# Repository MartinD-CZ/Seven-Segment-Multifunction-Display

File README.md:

# Seven Segment Multifunction Display
*see the article [here](http://embedblog.eu/?p=282)*

## Description
A simple project, based on the ATmega88. Can show analog voltage in two ranges (0 - 6 V or 0 - 30 V) with < 1 % accuracy or can display characters sent to it via UART/I2C.

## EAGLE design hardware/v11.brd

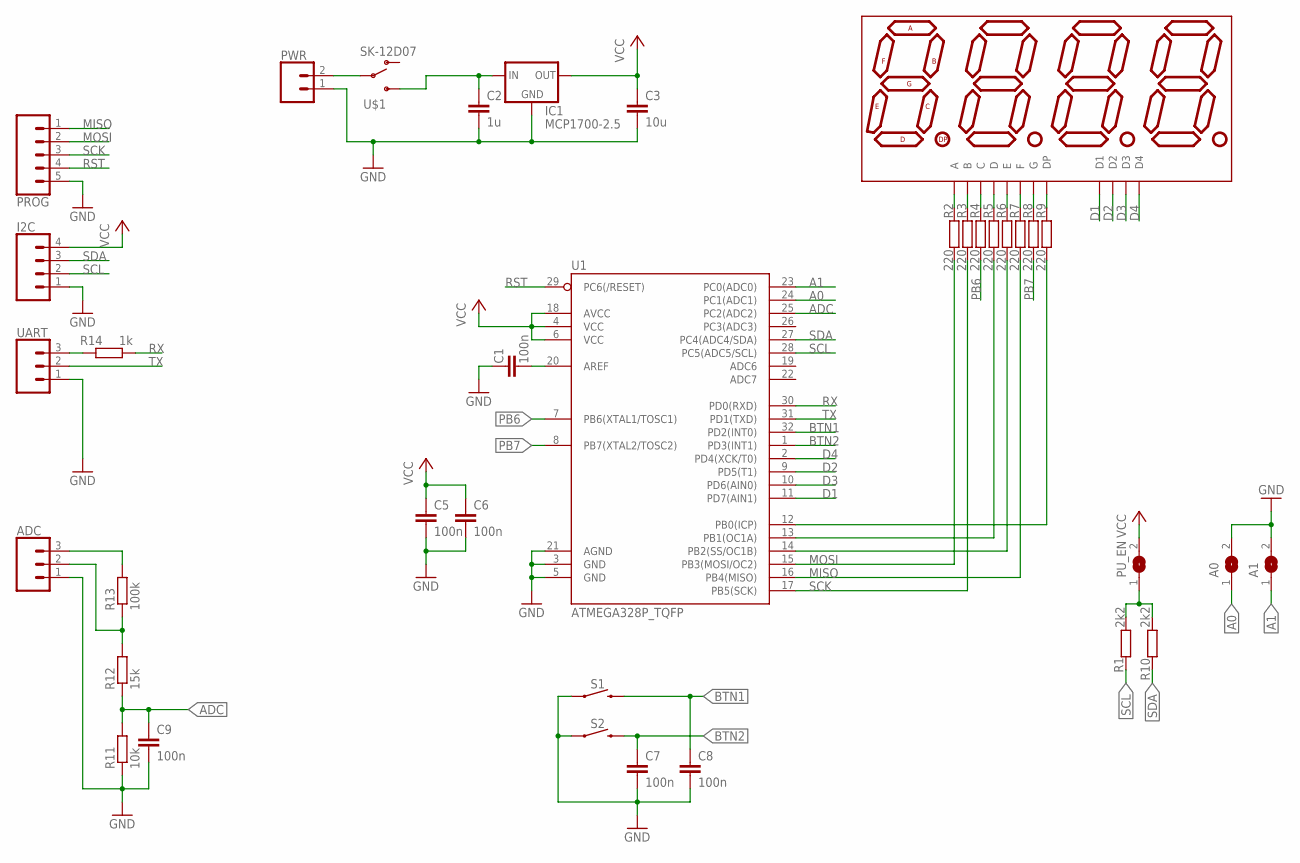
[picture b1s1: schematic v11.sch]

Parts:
A0, A1: SJ
ADC: 455-1750-1-ND; 1X03
C1, C5, C6, C7, C8, C9: 100n; C1206
C2: 1u; C1206
C3: 10u; C1206
D1: 7-SEG_0.56INCH; 7SEG_0.56INCH
I2C: CONN_04; 1X04
IC1: MCP1700-2.5; SOT23
PROG: CONN_05; 1X05
PU_EN: SJ
PWR: CONN_02; 1X02
R1, R10: 2k2; R1206
R2, R3, R4, R5, R6, R7, R8, R9: 220; R1206
R11: 10k; R1206
R12: 15k; R1206
R13: 100k; R1206
R14: 1k; R1206
S1, S2: MOMENTARY-SWITCH-SPST-PTH-6.0MM; TACTILE_SWITCH_PTH_6.0MM
U1: ATMEGA328P_TQFP; TQFP32-08
U$1: SK-12D07; SK12SWITCH
UART: 455-1750-1-ND; 1X03

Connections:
+3V3: C3.1, C5.1, C6.1, I2C.4, IC1.2 (OUT), PU_EN.2, U1.4 (VCC), U1.6 (VCC), U1.18 (AVCC)
A0: A0.1, U1.24 (PC1(ADC1))
A1: A1.1, U1.23 (PC0(ADC0))
ADC: C9.1, R11.2, R12.1, U1.25 (PC2(ADC2))
BTN1: C8.1, S1.3 (2), U1.32 (PD2(INT0))
BTN2: C7.1, S2.3 (2), U1.1 (PD3(INT1))
D1: D1.D1, U1.11 (PD7(AIN1))
D2: D1.D2, U1.9 (PD5(T1))
D3: D1.D3, U1.10 (PD6(AIN0))
D4: D1.D4, U1.2 (PD4(XCK/T0))
GND: A0.2, A1.2, ADC.1, C1.1, C2.2, C3.2, C5.2, C6.2, C7.2, C8.2, C9.2, I2C.1, IC1.1 (GND), PROG.5, PWR.1, R11.1, S1.1, S2.1, U1.3 (GND), U1.5 (GND), U1.21 (AGND), UART.1
MISO: PROG.1, R7.1, U1.16 (PB4(MISO))
MOSI: PROG.2, R2.1, U1.15 (PB3(MOSI/OC2))
unnamed: PWR.2, U$1.P2
unnamed: C2.1, IC1.3 (IN), U$1.IN (S)
unnamed: PU_EN.1, R1.2, R10.2
unnamed: R14.2, UART.3
unnamed: ADC.3, R13.2
unnamed: ADC.2, R12.2, R13.1
unnamed: D1.A, R2.2
unnamed: D1.B, R3.2
unnamed: D1.C, R4.2
unnamed: D1.D, R5.2
unnamed: D1.E, R6.2
unnamed: D1.F, R7.2
unnamed: D1.G, R8.2
unnamed: D1.DP, R9.2
unnamed: C1.2, U1.20 (AREF)
unnamed: R6.1, U1.14 (PB2(SS/OC1B))
unnamed: R5.1, U1.13 (PB1(OC1A))
unnamed: R9.1, U1.12 (PB0(ICP))
PB6: R4.1, U1.7 (PB6(XTAL1/TOSC1))
PB7: R8.1, U1.8 (PB7(XTAL2/TOSC2))
RST: PROG.4, U1.29 (PC6(/RESET))
RX: R14.1, U1.30 (PD0(RXD))
SCK: PROG.3, R3.1, U1.17 (PB5(SCK))
SCL: I2C.2, R1.1, U1.28 (PC5(ADC5/SCL))
SDA: I2C.3, R10.1, U1.27 (PC4(ADC4/SDA))
TX: U1.31 (PD1(TXD)), UART.2

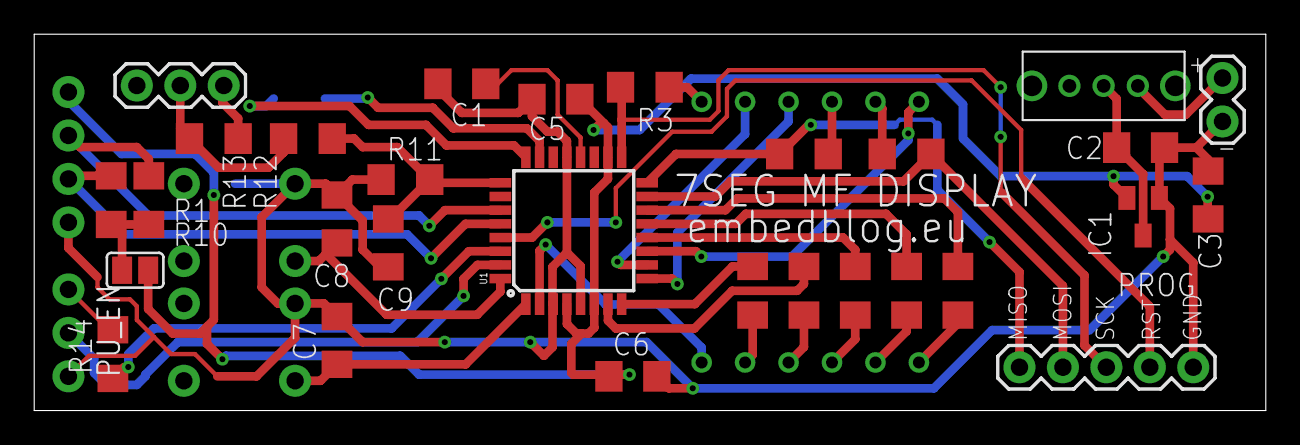
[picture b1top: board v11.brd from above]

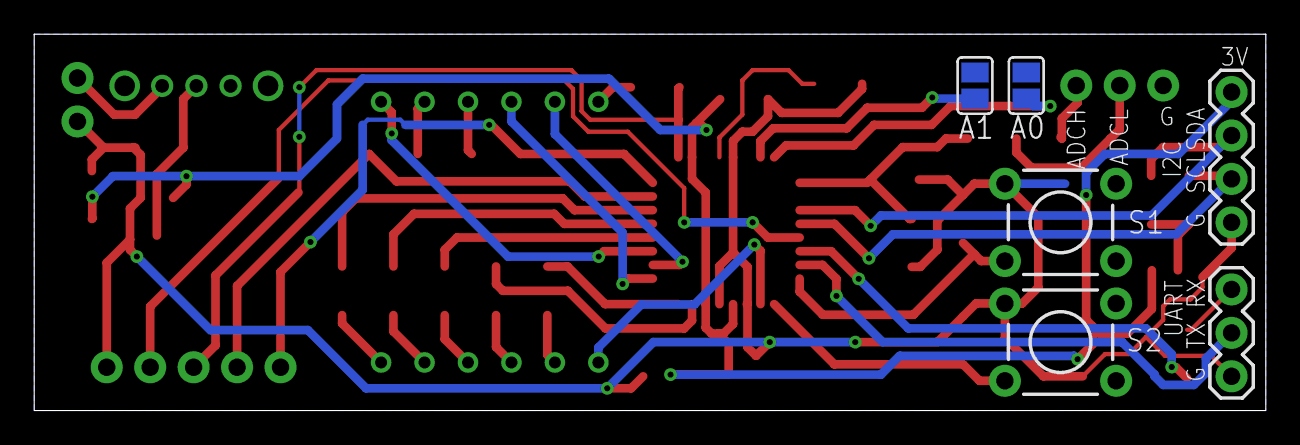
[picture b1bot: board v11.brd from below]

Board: 2 copper layers, 72.0 x 22.0 mm, 36 parts (7 on the bottom side), 39 nets.

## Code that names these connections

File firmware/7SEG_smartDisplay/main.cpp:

/*
 * 7SEG_smartDisplay.cpp
 * SEVEN SEGMENT MULTIFUNCTION DISPLAY	
 *
 * Author: martin@embedblog.eu
 * http://embedblog.eu/?p=282
 */ 

#include <avr/io.h>
#include "defines.h"
#include <util/delay.h>
#include <avr/interrupt.h>
#include "adc.h"
#include "uart.h"
#include "i2c.h"

const static float ADCL_GAIN = (R11_VALUE + R12_VALUE) / R11_VALUE;
const static float ADCH_GAIN = (R11_VALUE + R12_VALUE + R13_VALUE) / (10 * R11_VALUE);

volatile uint8_t display_digits[4];
volatile uint8_t display_pos;
volatile uint8_t decimal_pos;	//four LSBs correspond to the DPs

volatile uint8_t mode;
volatile bool mode_changed = true;
volatile bool hold;
volatile bool s1_pressed;

extern volatile uint8_t uart_output[4];
extern volatile uint8_t uart_outputDecimal;

extern volatile uint8_t i2c_output[4];
extern volatile uint8_t i2c_outputDecimal;

volatile uint8_t counter_25ms;

int main(void)
{
    //GPIO setup
	DDRB = 0xFF;
	DDRD = (1 << DDD4) | (1 << DDD5) | (1 << DDD6) | (1 << DDD7);

	//ADC setup
	adc_init();

	//UART setup
	uart_init();

	//I2C setup
	i2c_init();

	//INT setup
	PORTD = (1 << PD2) | (1 << PD3);
	EICRA = (1 << ISC11) | (1 << ISC01);
	EIMSK = (1 << INT1) | (1 << INT0);
	
	//TIMER0 setup - used to multiplex the display at around 500 Hz
	TCCR0B = (1 << CS00) | (1 << CS01);
	TIMSK0 = (1 << TOIE0);

	//TIMER2 setup - used to keep time (interrupt every 25 ms)
	TCCR2B = (1 << WGM21) | (1 << CS20) | (1 << CS21) | (1 << CS22);
	OCR2A = 195;
	TIMSK2 = (1 << OCIE2A);

	sei();

    while (1) 
    {
		uint16_t adc_result = adc_getResult();
		switch (mode)
		{
			case MODE_ADCL:
			{
				if (mode_changed)
				{
					decimal_pos = 0x00;
					mode_changed = false;
					SET_DISPLAY(CHAR_A, CHAR_D, CHAR_C, CHAR_L);
					_delay_ms(TRANSITION_TIME);
				}
				
				decimal_pos = 0b1000;
				adc_result *= ADCL_GAIN;
				for (int8_t i = 3; i >= 0; i --)
				{
					display_digits[i] = adc_result % 10;
					adc_result /= 10;
				}

				while (hold);
				break;
			}
			case MODE_ADCH:
			{
				if (mode_changed)
				{
					decimal_pos = 0x00;
					mode_changed = false;
					SET_DISPLAY(CHAR_A, CHAR_D, CHAR_C, CHAR_H);
					_delay_ms(TRANSITION_TIME);
				}
				
				decimal_pos = 0b0100;
				adc_result *= ADCH_GAIN;
				for (int8_t i = 3; i >= 0; i --)
				{
					display_digits[i] = adc_result % 10;
					adc_result /= 10;
				}

				while (hold);
				break;
			}
			case MODE_UART:
			{
				if (mode_changed)
				{
					decimal_pos = 0x00;
					mode_changed = false;
					SET_DISPLAY(CHAR_U, CHAR_A, CHAR_R, CHAR_T);
					_delay_ms(TRANSITION_TIME);
				}

				if (s1_pressed)
				{
					s1_pressed = false;
					decimal_pos = 0b0010;
					switch (uart_changeBaud())
					{
						case 0: {SET_DISPLAY(CHAR_BLANK, CHAR_BLANK, 9, 6); break;}
						case 1: {SET_DISPLAY(CHAR_BLANK, 1, 9, 2); break;}
						case 2: {SET_DISPLAY(CHAR_BLANK, 3, 8, 4); break;}
						case 3: {SET_DISPLAY(CHAR_BLANK, 5, 7, 6); break;}
						case 4: {SET_DISPLAY(1, 1, 5, 2); break;}
						case 5: {SET_DISPLAY(1, 0, 0, 0); decimal_pos = 0x00; break;}
					}

					_delay_ms(TRANSITION_TIME);
				}

				decimal_pos = uart_outputDecimal;
				SET_DISPLAY(uart_output[0], uart_output[1], uart_output[2], uart_output[3]);
				break;
			}
			case MODE_I2C:
			{
				if (mode_changed)
				{
					decimal_pos = 0x00;
					mode_changed = false;
					SET_DISPLAY(CHAR_BLANK, CHAR_I, 2, CHAR_C);
					_delay_ms(TRANSITION_TIME);
				}
				
				decimal_pos = i2c_outputDecimal;
				SET_DISPLAY(i2c_output[0], i2c_output[1], i2c_output[2], i2c_output[3]);
				break;
			}
		}

		_delay_ms(1000 / REFRESH_RATE);
    }
}

//timer 0 - used to multiplex the display
ISR(TIMER0_OVF_vect)
{
	display_pos++;
	if (display_pos > 3)
		display_pos = 0;

	PORTD |= 0b11110000;
	switch (display_pos)
	{
		case 0:
		{
			PORTB = charMap[display_digits[0]];
			if ((decimal_pos >> 3) & 0x01)
				PORTB |= 0x01;
			PORTD &=~(1 << PD7);
			break;
		}
		case 1:
		{
			PORTB = charMap[display_digits[1]];
			if ((decimal_pos >> 2) & 0x01)
				PORTB |= 0x01;
			PORTD &=~(1 << PD5);
			break;
		}
		case 2:
		{
			PORTB = charMap[display_digits[2]];
			if ((decimal_pos >> 1) & 0x01)
				PORTB |= 0x01;
			PORTD &=~(1 << PD6);
			break;
		}
		case 3:
		{
			PORTB = charMap[display_digits[3]];
			if (decimal_pos & 0x01)
				PORTB |= 0x01;
			PORTD &=~(1 << PD4);
			break;
		}
	}
}

//interrupt every 25 ms
ISR(TIMER2_COMPA_vect)
{
	counter_25ms++;
}

//button S1
ISR(INT0_vect)
{
	hold = !hold;
	s1_pressed = true;
}

//button S2
ISR(INT1_vect)
{
	mode_changed = true;
	mode++;
	if (mode >= MODES_NUMBER)
		mode = 0;
}

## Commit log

2019-05-09 V1.1
    initial commit

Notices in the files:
parts and their libraries:
SparkFun-Connectors: Licensing: Creative Commons ShareAlike 4.0 International - https://creativecommons.org/licenses/by-sa/4.0
